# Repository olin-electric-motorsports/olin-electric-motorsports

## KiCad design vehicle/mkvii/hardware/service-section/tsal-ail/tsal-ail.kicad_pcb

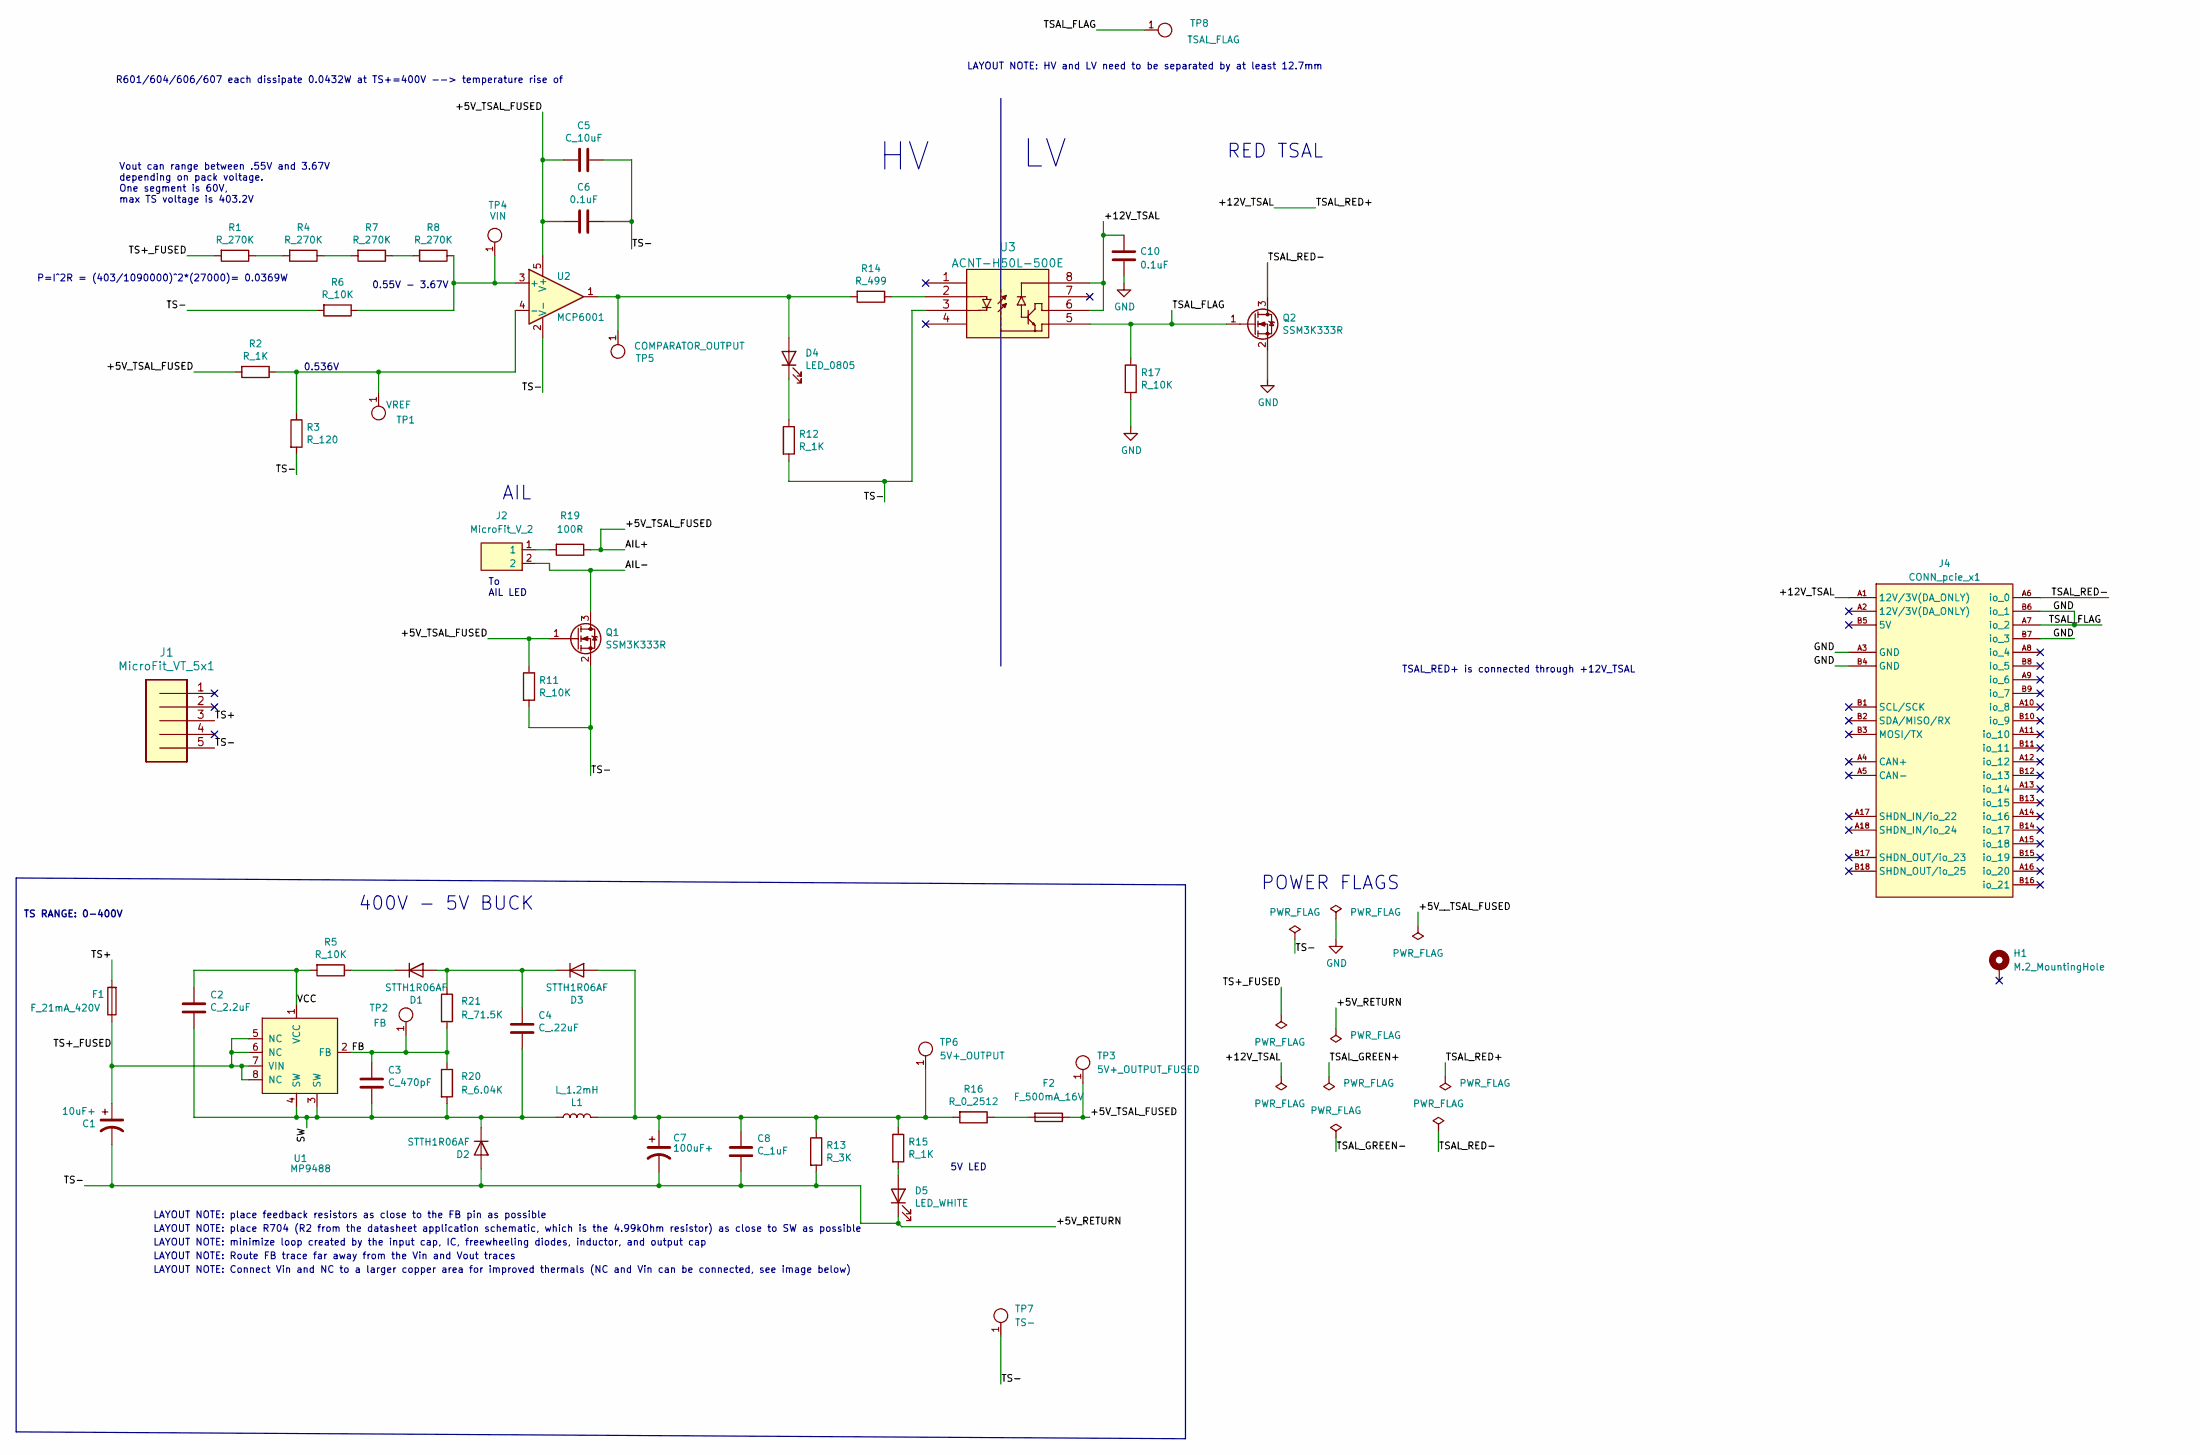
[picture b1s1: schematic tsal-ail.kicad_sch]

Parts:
C1: 10uF+; CP_Radial_D10.0mm_P5.00mm; MPN 450BXC10MEFC10X20
C2: C_2.2uF; C_0603; MPN GRM188R61E225KA12J
C3: C_470pF; C_0603; MPN 0603B471K500CT
C4: C_.22uF; C_0603; MPN CL10A224KB8NNNC
C5: C_10uF; C_0603; MPN LMK107BBJ106KALT
C6, C10: 0.1uF; C_0603; MPN CL10B104KB8NNWC
C7: 100uF+; CP_Radial_D8.0mm_P3.50mm; MPN ESK107M050AG3EA
C8: C_1uF; C_0603; MPN CL10B105KA8NNNC
D1, D2, D3: STTH1R06AF; D_SOD-128; MPN STTH1R06AF
D4: LED_0805; CHIPLED_0805; MPN LTST-C170KFKT
D5: LED_WHITE; CHIPLED_0805; MPN B1701TW--20P000314U1930
F1: F_21mA_420V; MPN B59884C0120A054
F2: F_500mA_16V; Fuse_1210; MPN 0ZCH0050FF2G
H1: M.2_MountingHole; M.2_Mount
J1: MicroFit_VT_5x1; Connector_MicroFit_VT_5x1; MPN 436500515
J2: MicroFit_V_2; MPN 0430450212
J4: CONN_pcie_x1; pcie_x1
L1: L_1.2mH; MPN RCP1317NP-122L
Q1, Q2: SSM3K333R; SOT-23F; MPN SSM3K333R,LF
R1, R4, R7, R8: R_270K; R_0603; MPN RMCF0603FT270K
R2, R12, R15: R_1K; R_0603; MPN RMCF0603FT1K00
R3: R_120; R_0603; MPN RC0603FR-13120RL
R5, R6, R11, R17: R_10K; R_0603; MPN RMCF0603FT10K0
R13: R_3K; R_0603; MPN RC0603FR-103KL
R14: R_499; R_0603; MPN RC0603FR-10499RL
R16: R_0_2512; R_2512_6332Metric; MPN CR2512-J/-000ELF
R19: 100R; R_0603; MPN RMCF0603FT100R
R20: R_6.04K; R_0603; MPN RMCF0603FT6K04
R21: R_71.5K; R_0603; MPN RMCF0603FT71K5
TP1: VREF; Test_Point_SMD; MPN 5019
TP2: FB; Test_Point_SMD; MPN 5019
TP3: 5V+_OUTPUT_FUSED; Test_Point_SMD; MPN 5019
TP4: VIN; Test_Point_SMD; MPN 5019
TP5: COMPARATOR_OUTPUT; Test_Point_SMD; MPN 5019
TP6: 5V+_OUTPUT; Test_Point_SMD; MPN 5019
TP7: TS-; Test_Point_SMD; MPN 5019
TP8: TSAL_FLAG; Test_Point_SMD; MPN 5019
U1: MP9488; Converter_DCDC_MPS_MP9488; MPN MP9488GS-Z
U2: MCP6001; SOT-353_SC-70-5; MPN MCP6001T-I/OT
U3: ACNT-H50L-500E; MPN ACNT-H50L-000E

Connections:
/+5V_RETURN: C1.2, C5.1, C6.1, C7.2, C8.2, D2.2 (A), D5.1 (K), J1.5, Q1.2 (S), R3.2, R6.2, R11.2, R12.2, R13.2, TP7.1, U2.2 (V-), U3.3
/+5V_TSAL_FUSED: C5.2, C6.2, F2.1, Q1.1 (G), R2.2, R11.1, R19.1, TP3.1, U2.5 (V+)
/+12V_TSAL: C10.1, J4.A1 (12V/3V(DA_ONLY)), U3.6, U3.8
/AIL-: J2.2, Q1.3 (D)
/FB: C3.1, R20.1, R21.2, TP2.1, U1.2 (FB)
/SW: C2.2, C3.2, C4.2, D2.1 (K), L1.1, R20.2, U1.3 (SW), U1.4 (SW)
/TS+: F1.2, J1.3
/TS+_FUSED: C1.1, F1.1, R1.2, U1.5 (NC), U1.6 (NC), U1.7 (VIN), U1.8 (NC)
/TSAL_RED-: J4.A6 (io_0), Q2.3 (D)
/VCC: C2.1, R5.2, U1.1 (VCC)
GND: C10.2, J4.A3 (GND), J4.A7 (io_2), J4.B4 (GND), J4.B6 (io_1), J4.B7 (io_3), Q2.1 (G), Q2.2 (S), R17.1, R17.2, TP8.1, U3.5
unnamed: C4.1, D1.2 (A), D3.1 (K), R21.1
unnamed: D1.1 (K), R5.1
unnamed: C7.1, C8.1, D3.2 (A), L1.2, R13.1, R15.1, R16.2, TP6.1
unnamed: D4.2 (A), R14.2, TP5.1, U2.1
unnamed: D4.1 (K), R12.1
unnamed: D5.2 (A), R15.2
unnamed: F2.2, R16.1
unnamed: J2.1, R19.2
unnamed: R1.1, R4.2
unnamed: R4.1, R7.2
unnamed: R7.1, R8.2
unnamed: R14.1, U3.2
unnamed: R6.1, R8.1, TP4.1, U2.3 (+)
unnamed: R2.1, R3.1, TP1.1, U2.4 (-)

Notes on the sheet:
TSAL_RED+ is connected through +12V_TSAL
LAYOUT NOTE: Route FB trace far away from the Vin and Vout traces
AIL
LAYOUT NOTE: minimize loop created by the input cap, IC, freewheeling diodes, inductor, and output cap
RED TSAL
LAYOUT NOTE: Connect Vin and NC to a larger copper area for improved thermals (NC and Vin can be connected, see image below)
P=I^2R = (403/1090000)^2*(27000)= 0.0369W
LAYOUT NOTE: place feedback resistors as close to the FB pin as possible
Vout can range between .55V and 3.67V depending on pack voltage. One segment is 60V, max TS voltage is 403.2V
LAYOUT NOTE: place R704 (R2 from the datasheet application schematic, which is the 4.99kOhm resistor) as close to SW as possible
LAYOUT NOTE: HV and LV need to be separated by at least 12.7mm
5V LED
POWER FLAGS
0.536V
R601/604/606/607 each dissipate 0.0432W at TS+=400V --> temperature rise of
0.55V - 3.67V
TS RANGE: 0-400V
To AIL LED
400V - 5V BUCK

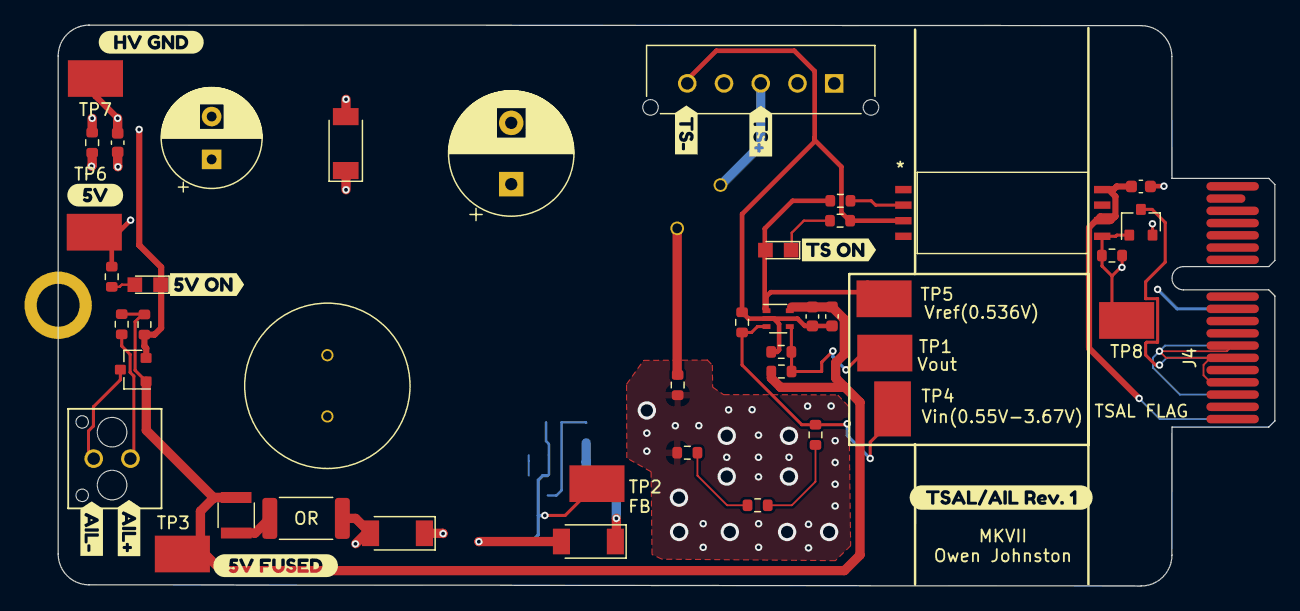
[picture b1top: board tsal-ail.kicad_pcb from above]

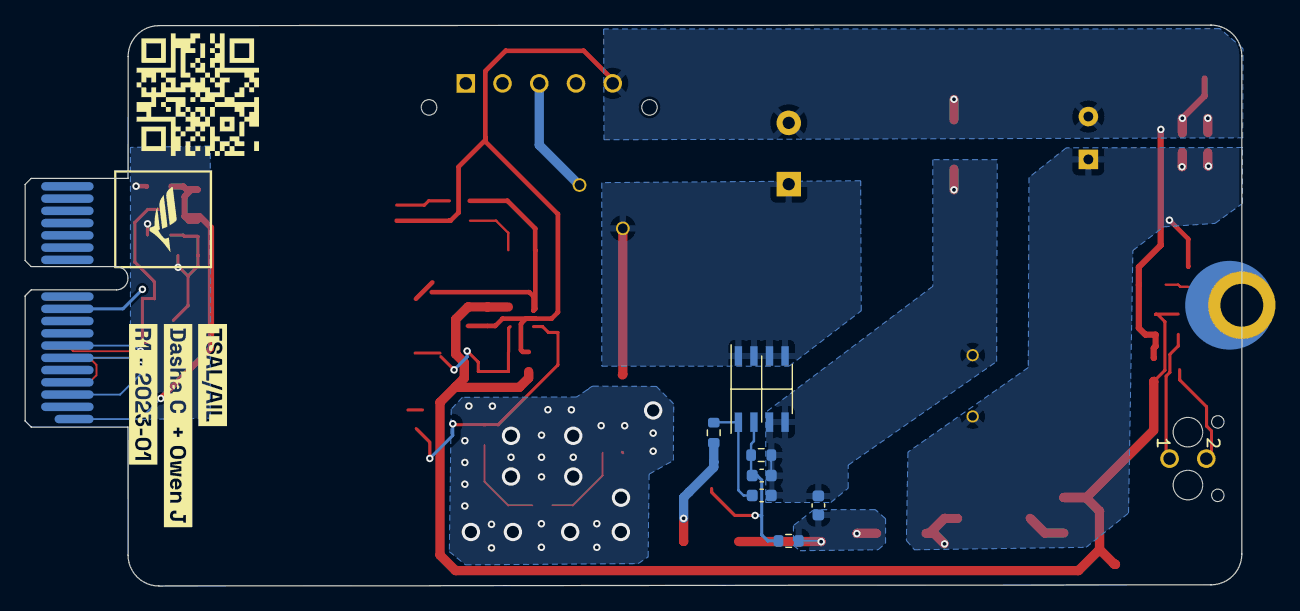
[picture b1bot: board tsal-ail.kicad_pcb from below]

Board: 2 copper layers, 99.3 x 45.8 mm, 66 parts (11 on the bottom side), 25 nets.

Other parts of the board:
QR*****: hw.oem.to/6_TSAL-AIL_1; QR_6_TSAL-AIL_1
kibuzzard-63AC91FD: G***; kibuzzard-63AC91FD
kibuzzard-63AC92E3: G***; kibuzzard-63AC92E3
kibuzzard-63AC93EB: G***; kibuzzard-63AC93EB
kibuzzard-63AC93FC: G***; kibuzzard-63AC93FC
kibuzzard-63AC9220: G***; kibuzzard-63AC9220
kibuzzard-63AC9283: G***; kibuzzard-63AC9283
kibuzzard-63AC9446: G***; kibuzzard-63AC9446
kibuzzard-63AC9456: G***; kibuzzard-63AC9456
kibuzzard-63AD023E: G***; kibuzzard-63AD023E
kibuzzard-63AD0077: G***; kibuzzard-63AD0077
kibuzzard-63BF4696: G***; kibuzzard-63BF4696
kibuzzard-63D843BA: G***; kibuzzard-63D843BA
kibuzzard-63D84460: G***; kibuzzard-63D84460

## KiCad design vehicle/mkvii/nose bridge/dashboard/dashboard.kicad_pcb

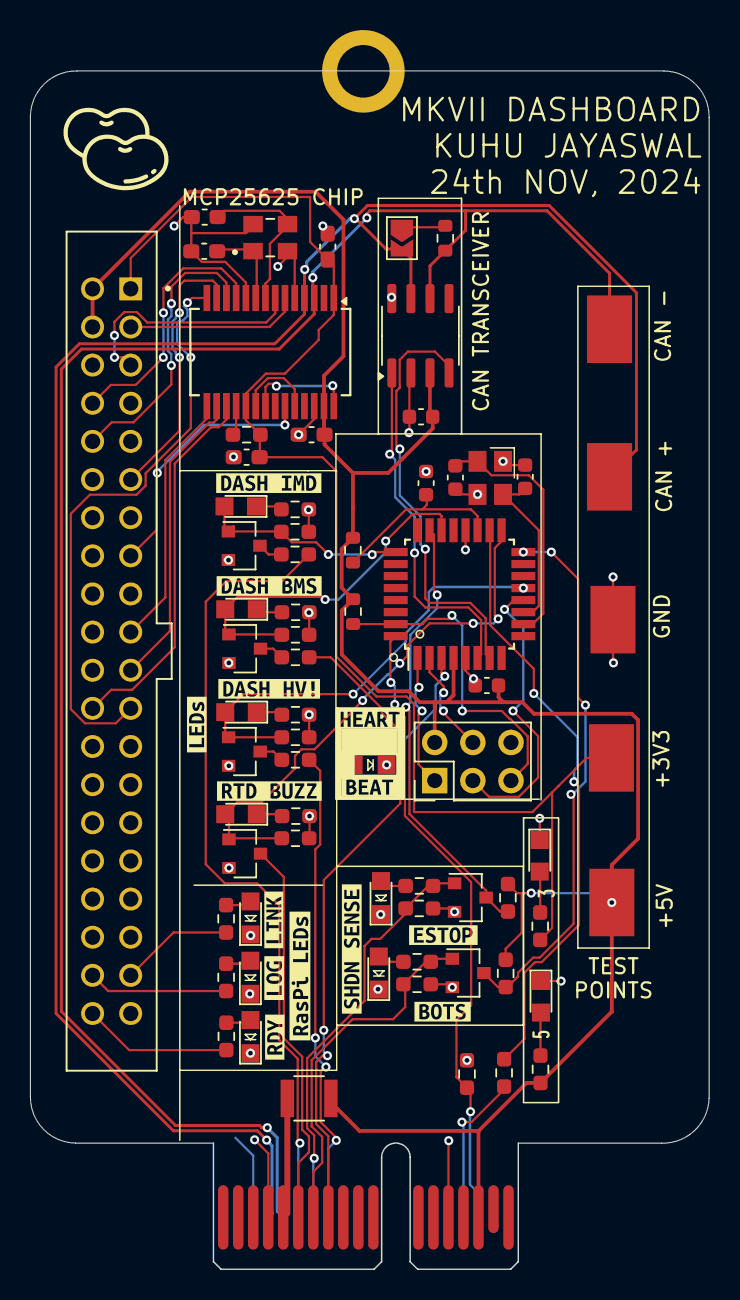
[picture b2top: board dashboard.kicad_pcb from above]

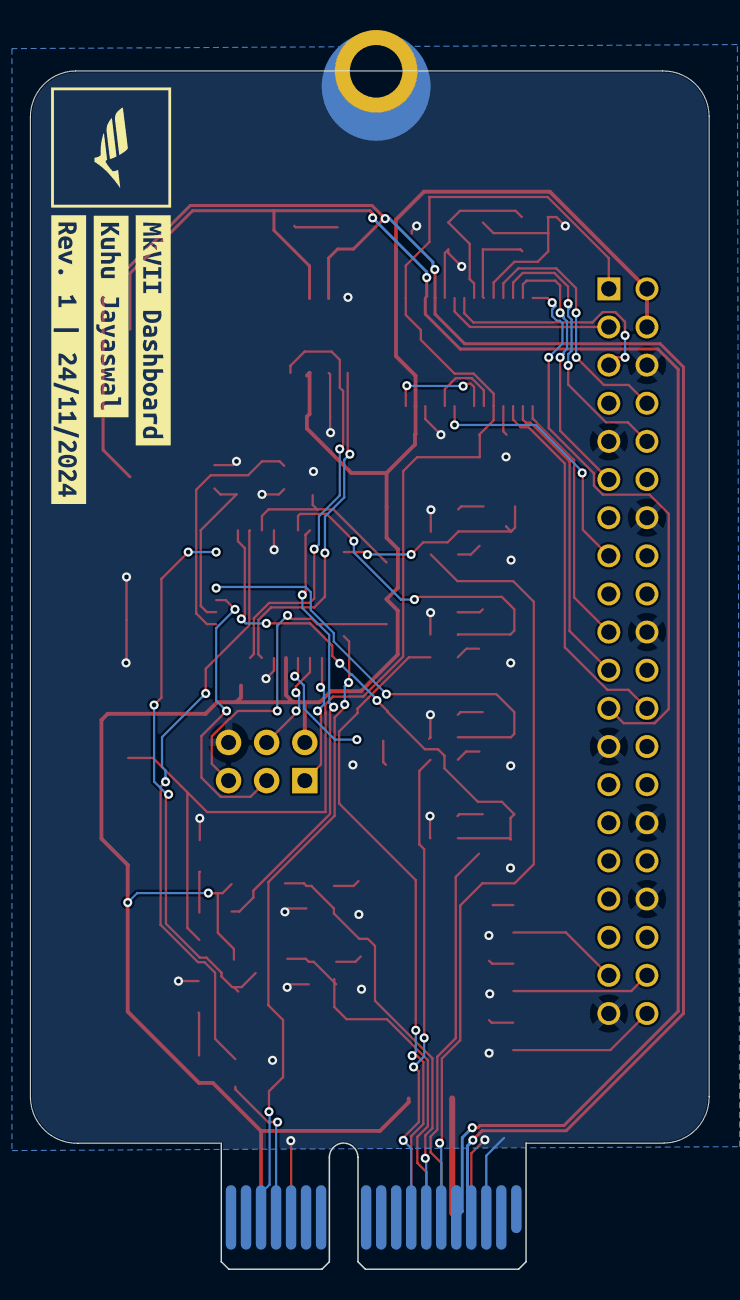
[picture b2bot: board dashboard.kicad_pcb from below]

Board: 2 copper layers, 45.2 x 79.8 mm, 90 parts (3 on the bottom side), 65 nets.

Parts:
C1, C5: 0u1F; C_0603
C2: 100pF; C_0603
C3, C4: 30pF; C_0603
C6, C7, C8: C_0.1uF; C_0603_1608Metric_Pad1.08x0.95mm_HandSolder
C9, C10: C_14pF; C_0603_1608Metric_Pad1.08x0.95mm_HandSolder
D1, D2: LED_0805; CHIPLED_0805
D3, D4, D5, D8: LED_0805; LED_0805_OEM
D6, D7: LED_BLUE; LED_0805_OEM
D9, D10, D11, D12: LED_AMBER; CHIPLED_0805
F1: F_500mA_16V; Fuse_1210
H1: CONN_MountingHole; PCIe_Mount
J1: Conn_02x20_Odd_Even; SULLINS_SFH11-PBPC-D20-ST-BK
J3: pcie_x1
J4: Conn_02x03_Odd_Even; PinHeader_2x03_P2.54mm_Vertical
JP1: SolderJumper_2_Open; SolderJumper-2_P1.3mm_Open_TrianglePad1.0x1.5mm
Q1, Q2, Q3, Q4, Q5, Q6: SSM3K333R; SOT-23F
R1, R2, R4, R5, R7, R10, R26: R_200; R_0603_1608Metric_Pad0.98x0.95mm_HandSolder
R3: 100R; R_0603
R6: R_10K; R_0603
R8: R_120_DNP; R_0603
R9, R18, R22, R25: R_10K; R_0603_1608Metric_Pad0.98x0.95mm_HandSolder
R11, R12, R13, R14, R15, R16, R17, R20, R23, R27, R28, R29, R30: R_1K; R_0603_1608Metric_Pad0.98x0.95mm_HandSolder
R21, R24: R_100K; R_0603_1608Metric_Pad0.98x0.95mm_HandSolder
TP1, TP2, TP3, TP4, TP5: Test_Point_SMD
U1: ATMEGA16M1; TQFP-32_7x7mm_Pitch0.8mm
U2: MCP2561-E-SN; SOIC-8_3.9x4.9mm_P1.27mm
U3: MCP25625-x-SS; SSOP-28_5.3x10.2mm_P0.65mm
Y1: Crystal_16MHz_18pF; Crystal_TXC7M
Y2: Crystal_8MHz_12pF; XTAL_ECS-240-8-33-AGN-TR
kibuzzard-67460C4D: G***; kibuzzard-67460C4D
kibuzzard-67461FCA: G***; kibuzzard-67461FCA
kibuzzard-67466F5D: G***; kibuzzard-67466F5D
kibuzzard-67466F8B: G***; kibuzzard-67466F8B
kibuzzard-67466FA1: G***; kibuzzard-67466FA1
kibuzzard-67468C5A: G***; kibuzzard-67468C5A
kibuzzard-674671EB: G***; kibuzzard-674671EB
kibuzzard-6746218C: G***; kibuzzard-6746218C
kibuzzard-6746500B: G***; kibuzzard-6746500B
kibuzzard-6746505F: G***; kibuzzard-6746505F
kibuzzard-6746515A: G***; kibuzzard-6746515A
kibuzzard-6746703E: G***; kibuzzard-6746703E
kibuzzard-67462150: G***; kibuzzard-67462150
kibuzzard-67462179: G***; kibuzzard-67462179
kibuzzard-67465001: G***; kibuzzard-67465001
kibuzzard-67467063: G***; kibuzzard-67467063
kibuzzard-67467243: G***; kibuzzard-67467243

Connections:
+3V3: C6.1, C7.1, J1.1, R2.1, R18.2, TP4.1, U3.1 (VIO), U3.19 (VDD)
+5V: C1.1, C5.1, C8.2, F1.1, J1.2, J1.4, J3.B16 (io_21), J4.2, R1.1, R3.1, R6.2, R22.1, R25.1, TP3.1, U1.4 (VCC), U2.3 (VDD), U3.27 (VDDA)
/AMS_LED_LOW_SIDE: J3.B8 (io_5), R14.1
/AMS_LED_LSD: D10.2 (A), Q2.1 (G), R15.1, U1.22 ((PCINT14/ADC10/ACMP1)PC6)
/BOTS_SHDN_SENSE: Q6.3 (D), R25.2, U1.16 ((PCINT2/ADC5/INT1/ACMPN0)PB2)
/CAN_+: J3.A4 (CAN+), JP1.2 (B), TP2.1, U2.7 (CANH), U3.4 (CANH)
/CAN_-: J3.A5 (CAN-), R8.2, TP5.1, U2.6 (CANL), U3.3 (CANL)
/CAN_RX: U1.7 ((PCINT11/T1/ICP1B/RXCAN)PC3), U2.4 (RXD)
/CAN_TX: U1.6 ((PCINT10/T0/TXCAN)PC2), U2.1 (TXD)
/E_STOP_SHDN_SENSE: Q5.3 (D), R22.2, U1.23 ((PCINT3/AMP0-)PB3)
/HEARTBEAT: R26.1, U1.3 ((PCINT9/PSCIN1/OC1B/~SS_A)PC1)
/HV_LED_LOW_SIDE: J3.A8 (io_4), R17.1
/HV_LED_LSD: D12.2 (A), Q4.1 (G), R30.1, U1.13 ((PCINT21/ADC2/ACMP2)PD5)
/IMD_LED_LOW_SIDE: J3.A6 (io_0), R13.1
/IMD_LED_LSD: D9.2 (A), Q1.1 (G), R11.1, U1.25 ((PCINT15/D2A/AMP2+)PC7)
/MCP25625 Chip/RX_CAN: U3.21 (RxCAN), U3.28 (RXD)
/MCP25625 Chip/TX_CAN: U3.20 (TxCAN), U3.24 (TXD)
/MCP25625 Chip/~INT: J1.11, U3.13 (~INT)
/MCP25625 Chip/~RESET: R18.1, U3.18 (~RESET)
/MCP25625 Chip/~TX1RTS: J1.3, U3.6 (~Tx1RTS)
/MCP25625 Chip/~TX2RTS: J1.5, U3.7 (~Tx2RTS)
/MISO: J1.21, U3.16 (SO)
/MOSI: J1.19, U3.15 (SI)
/PROGRAMMING_LED_1: J1.40, R4.1
/PROGRAMMING_LED_2: J1.38, R5.1
/PROGRAMMING_LED_3: J1.37, R7.1
/RESET: J4.5, R6.1, U1.31 ((PCINT24/OCD/~RESET)PE0)
/RTD_BUTTON_LED+: R10.1, U1.18 ((PCINT13/ADC9/ACMP3/AMP1+)PC5)
/RTD_BUTTON_SENSE-: J3.A16 (io_20), R9.1, U1.32 ((PCINT17/CLKO/PSCIN0)PD1)
/RTD_BUZZER_LOW_SIDE: J3.B6 (io_1), Q3.3 (D)
/RTD_BUZZER_LSD: D11.2 (A), Q3.1 (G), R28.1, U1.17 ((PCINT12/ADC8/ACMPN3/AMP1-)PC4)
/SCK: J1.23, U3.14 (SCK)
/SS_BOTS: J3.B7 (io_3), Q6.1 (G), R23.1, R24.1
/SS_ESTOP_DRIVER: J3.A7 (io_2), Q5.1 (G), R20.1, R21.1
/~CS: J1.24, U3.17 (~CS)
/~RX0BF: J1.10, U3.12 (~Rx0BF)
/~RX1BF: J1.8, U3.11 (~Rx1BF)
/~TX0RTS: J1.15, U3.23 (~Tx0RTS)
GND: C1.2, C2.2, C3.2, C4.2, C5.2, C6.2, C7.2, C8.1, C9.2, C10.2, D1.1 (K), D2.1 (K), D3.1 (K), D4.1 (K), D5.1 (K), D6.1 (K), D7.1 (K), D8.1 (K), H1.1, J1.6, J1.9, J1.14, J1.20, J1.25, J1.30, J1.34, J1.39, J3.A3 (GND), J3.B4 (GND), J3.B14 (io_17), J4.6, Q1.2 (S), Q2.2 (S), Q3.2 (S), Q4.2 (S), Q5.2 (S), Q6.2 (S), R9.2, R11.2, R12.2, R15.2, R16.2, R21.2, R24.2, R27.2, R28.2, R29.2, R30.2, TP1.1, U1.5 (GND), U1.20 (AGND), U2.2 (VSS), U2.8 (STBY), U3.5 (STBY), U3.10 (GND), U3.26 (VSS), Y1.2, Y1.4, Y2.2, Y2.4
unnamed: D1.2 (A), R1.2
unnamed: D2.2 (A), R2.2
unnamed: D3.2 (A), R4.2
unnamed: D4.2 (A), R5.2
unnamed: D5.2 (A), R7.2
unnamed: D6.2 (A), R20.2
unnamed: D7.2 (A), R23.2
unnamed: D8.2 (A), R26.2
unnamed: D9.1 (K), R27.1
unnamed: D10.1 (K), R12.1
unnamed: D11.1 (K), R16.1
unnamed: D12.1 (K), R29.1
unnamed: F1.2, J3.B5 (5V)
unnamed: J3.A15 (io_18), R10.2
unnamed: J4.1, U1.1 ((PCINT18/PSCIN2/OC1A/MISO_A)PD2)
unnamed: J4.3, U1.12 ((PCINT20/ADC1/RXD/RXLIN/ICP1A/SCK_A)PD4)
unnamed: J4.4, U1.2 ((PCINT19/TXD/TXLIN/OC0A/~SS/MOSI_A)PD3)
unnamed: JP1.1 (A), R8.1
unnamed: Q1.3 (D), R13.2
unnamed: Q2.3 (D), R14.2
unnamed: Q4.3 (D), R17.2
unnamed: C4.1, U1.10 ((PCINT25/OC0B/XTAL1)PE1), Y1.1
unnamed: C3.1, U1.11 ((PCINT26/ADC0/XTAL2)PE2), Y1.3
unnamed: C2.1, R3.2, U1.19 (AVCC)
unnamed: C9.1, U3.9 (OSC1), Y2.1
unnamed: C10.1, U3.8 (OSC2), Y2.3

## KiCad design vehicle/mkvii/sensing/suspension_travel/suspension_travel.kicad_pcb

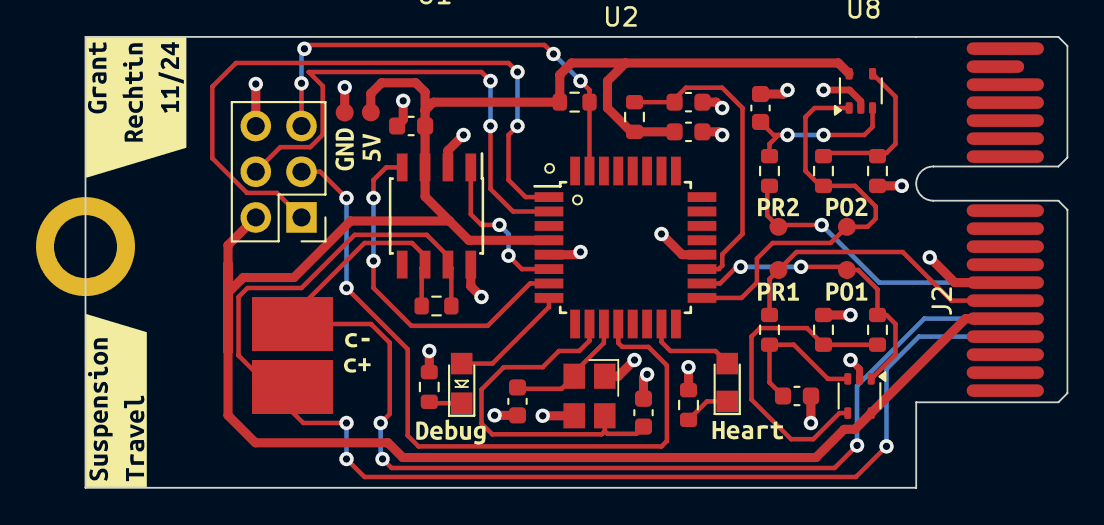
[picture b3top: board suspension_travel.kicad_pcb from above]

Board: 2 copper layers, 54.6 x 25.0 mm, 48 parts (0 on the bottom side), 25 nets.

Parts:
5VTestPoint1: TestPoint; TestPoint_Pad_D1mm
C1, C3, C6, C7: C_0.1uF; C_0603
C2: C_100pF; C_0603
C4, C5: C_30pF; C_0603
Can+Tp1: TestPoint; Test_Point_SMD
Can-TP1: TestPoint; Test_Point_SMD
D1: LED_0805; LED_0805_OEM
D2: LED_AMBER; CHIPLED_0805
GND1: TestPoint; TestPoint_Pad_D1mm
H1: CONN_MountingHole; PCIe_Mount
J1: CONN_02X03; PinHeader_2x03_P2.54mm_Vertical
J2: CONN_pcie_x1; pcie_x1
LP1_POST1, LP1_PRE1, LP2_POST1, LP2_PRE1: TestPoint; TestPoint_Pad_D1mm
R1, R4, R5, R6, R9, R10: R_100; R_0603
R2: R_120_DNP; R_0603
R3: R_10K; R_0603
R7, R8: R_200; R_0603
R11: R_1K; R_0603
U1: MCP2561-E_SN; SOIC-8_3.9x4.9mm_Pitch1.27mm_OEM
U2: ATMEGA16M1; TQFP-32_7x7mm_Pitch0.8mm
U3, U8: U_OPAMP_MCP6001; SOT-353_SC-70-5
Y1: Crystal_SMD; Crystal_TXC7M
kibuzzard-673FD6A4: G***; kibuzzard-673FD6A4
kibuzzard-673FD6B3: G***; kibuzzard-673FD6B3
kibuzzard-673FD6DC: G***; kibuzzard-673FD6DC
kibuzzard-673FD6EA: G***; kibuzzard-673FD6EA
kibuzzard-673FD6F4: G***; kibuzzard-673FD6F4
kibuzzard-673FD70C: G***; kibuzzard-673FD70C
kibuzzard-673FD675: G***; kibuzzard-673FD675
kibuzzard-673FD704: G***; kibuzzard-673FD704
kibuzzard-673FD725: G***; kibuzzard-673FD725
kibuzzard-673FD744: G***; kibuzzard-673FD744
kibuzzard-6740EEA9: G***; kibuzzard-6740EEA9
kibuzzard-6740EF04: G***; kibuzzard-6740EF04

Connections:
+5V: 5VTestPoint1.1, C1.1, C3.1, J1.2, J2.B5 (5V), R1.1, R3.1, U1.3 (VDD), U2.4 (VCC), U3.5 (V+), U8.5 (V+)
/CAN_+: Can+Tp1.1, J2.A4 (CAN+), R2.1, U1.7 (CANH)
/CAN_-: Can-TP1.1, J2.A5 (CAN-), R2.2, U1.6 (CANL)
/CAN_RX: U1.4 (RXD), U2.7 ((PCINT11/T1/ICP1B/RXCAN)PC3)
/CAN_TX: U1.1 (TXD), U2.6 ((PCINT10/T0/TXCAN)PC2)
/DEBUG_LED: D1.2 (A), U2.8 ((PCINT0/MISO/PSCOUT2A)PB0)
/Heartbeat: D2.2 (A), U2.15 ((PCINT23/ACMP0)PD7)
/MISO: J1.1, U2.1 ((PCINT18/PSCIN2/OC1A/MISO_A)PD2)
/MOSI: J1.4, U2.2 ((PCINT19/TXD/TXLIN/OC0A/~SS/MOSI_A)PD3)
/RESET: J1.5, R3.2, U2.31 ((PCINT24/OCD/~RESET)PE0)
/SCK: J1.3, U2.12 ((PCINT20/ADC1/RXD/RXLIN/ICP1A/SCK_A)PD4)
/lp1_Vout: J2.B6 (io_1), LP1_PRE1.1, R5.1
/lp1_fVout: LP1_POST1.1, R9.1, U2.18 ((PCINT13/ADC9/ACMP3/AMP1+)PC5), U3.1
/lp2_Vout: J2.A7 (io_2), LP2_PRE1.1, R6.1
/lp2_fVout: LP2_POST1.1, R10.1, U2.17 ((PCINT12/ADC8/ACMPN3/AMP1-)PC4), U8.1
GND: C1.2, C2.2, C3.2, C4.2, C5.2, C6.2, C7.2, GND1.1, H1.1, J1.6, J2.A3 (GND), J2.A6 (io_0), J2.B4 (GND), J2.B7 (io_3), R4.2, R7.1, R8.1, R11.2, U1.2 (VSS), U1.8 (STBY), U2.5 (GND), U2.20 (AGND), U3.2 (V-), U8.2 (V-), Y1.2, Y1.4
unnamed: D1.1 (K), R4.1
unnamed: D2.1 (K), R11.1
unnamed: C5.1, U2.10 ((PCINT25/OC0B/XTAL1)PE1), Y1.3
unnamed: C4.1, U2.11 ((PCINT26/ADC0/XTAL2)PE2), Y1.1
unnamed: C2.1, R1.2, U2.19 (AVCC)
unnamed: C6.1, R5.2, U3.3 (+)
unnamed: R7.2, R9.2, U3.4 (-)
unnamed: C7.1, R6.2, U8.3 (+)
unnamed: R8.2, R10.2, U8.4 (-)

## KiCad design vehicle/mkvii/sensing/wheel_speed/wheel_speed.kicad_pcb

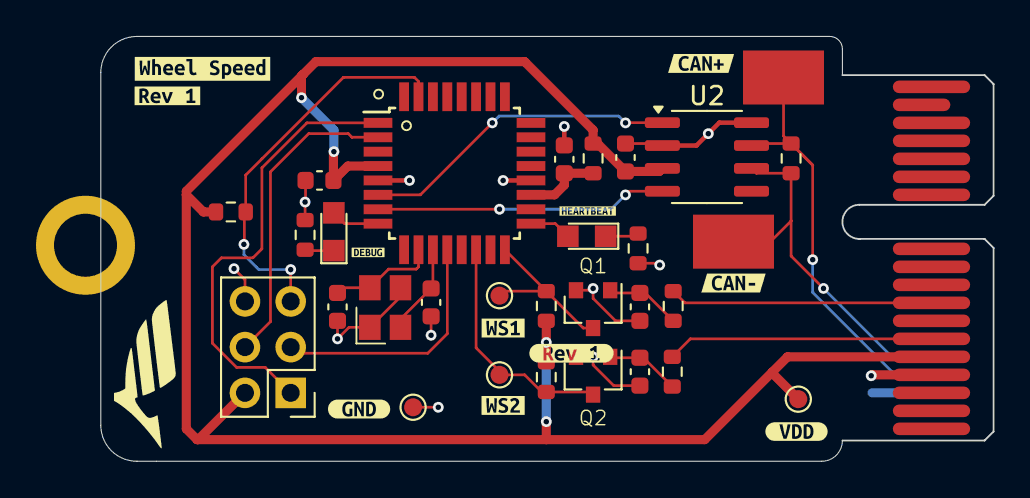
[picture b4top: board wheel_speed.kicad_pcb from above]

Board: 2 copper layers, 49.6 x 23.6 mm, 43 parts (1 on the bottom side), 23 nets.

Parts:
C1: C_0.1uF; C_0603
C2: C_100pF; C_0603
C3: 0u1F; C_0603
C4, C5: C_30pF; C_0603
C6, C7: 10nF; C_0603
D1, D2: LED_BLUE; CHIPLED_0805
GND1: TestPoint; TestPoint_Pad_D1.0mm
J1: CONN_02x03; PinHeader_2x03_P2.54mm_Vertical
J2: pcie_x1
Q1, Q2: SSM3K333R; SOT-23F
R1, R4, R9: R_100; R_0603
R2: R_120_DNP; R_0603
R3: R_10K; R_0603
R5, R7: 1K; R_0603
R6, R8: R_1K_DNP; R_0603
TP1, TP2: TP_SMD; Test_Point_SMD
U1: ATMEGA16M1; TQFP-32_7x7mm_Pitch0.8mm
U2: MCP2561-E-SN; SOIC-8_3.9x4.9mm_P1.27mm
VDD1: TestPoint; TestPoint_Pad_D1.0mm
WS1, WS2: TestPoint; TestPoint_Pad_D1.0mm
Y1: Crystal_16MHz_18pF; Crystal_TXC7M
kibuzzard-673FD414: G***; kibuzzard-673FD414
kibuzzard-6733FF5C: G***; kibuzzard-6733FF5C
kibuzzard-6733FF7D: G***; kibuzzard-6733FF7D
kibuzzard-6733FF15: G***; kibuzzard-6733FF15
kibuzzard-6733FF25: G***; kibuzzard-6733FF25
kibuzzard-6733FF69: G***; kibuzzard-6733FF69
kibuzzard-67434F9F: G***; kibuzzard-67434F9F
kibuzzard-674351E2: G***; kibuzzard-674351E2
kibuzzard-674352C6: G***; kibuzzard-674352C6
kibuzzard-67435037: G***; kibuzzard-67435037
kibuzzard-67435047: G***; kibuzzard-67435047
kibuzzard-67435202: G***; kibuzzard-67435202

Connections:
+5V: C1.1, C3.2, J1.2, J2.B5 (5V), R1.1, R3.2, R6.1, R8.1, U1.4 (VCC), U2.3 (VDD), VDD1.1
/CAN_+: J2.A4 (CAN+), R2.1, TP2.1, U2.7 (CANH)
/CAN_-: J2.A5 (CAN-), R2.2, TP1.1, U2.6 (CANL)
/CAN_RX: U1.7 ((PCINT11/T1/ICP1B/RXCAN)PC3), U2.4 (RXD)
/CAN_TX: U1.6 ((PCINT10/T0/TXCAN)PC2), U2.1 (TXD)
/DEBUG_LED: D1.2 (A), U1.8 ((PCINT0/MISO/PSCOUT2A)PB0)
/HEARTBEAT_LED: D2.2 (A), U1.17 ((PCINT12/ADC8/ACMPN3/AMP1-)PC4)
/MISO: J1.1, U1.1 ((PCINT18/PSCIN2/OC1A/MISO_A)PD2)
/MOSI: J1.4, U1.2 ((PCINT19/TXD/TXLIN/OC0A/~SS/MOSI_A)PD3)
/RESET: J1.5, R3.1, U1.31 ((PCINT24/OCD/~RESET)PE0)
/SCK: J1.3, U1.12 ((PCINT20/ADC1/RXD/RXLIN/ICP1A/SCK_A)PD4)
/ws1_Vout: J2.B8 (io_5), R7.1
/ws1_fVout: Q1.3 (D), R8.2, U1.16 ((PCINT2/ADC5/INT1/ACMPN0)PB2), WS1.1
/ws2_Vout: J2.B6 (io_1), R5.1
/ws2_fVout: Q2.3 (D), R6.2, U1.14 ((PCINT22/ADC3/INT0/ACMPN2)PD6), WS2.1
GND: C1.2, C2.2, C3.1, C4.2, C5.2, C6.2, C7.2, GND1.1, J1.6, J2.A3 (GND), J2.B4 (GND), Q1.2 (S), Q2.2 (S), R4.2, R9.2, U1.5 (GND), U1.20 (AGND), U2.2 (VSS), U2.8 (STBY), Y1.2, Y1.4
unnamed: D1.1 (K), R4.1
unnamed: D2.1 (K), R9.1
unnamed: C6.1, Q1.1 (G), R7.2
unnamed: C7.1, Q2.1 (G), R5.2
unnamed: C5.1, U1.10 ((PCINT25/OC0B/XTAL1)PE1), Y1.3
unnamed: C4.1, U1.11 ((PCINT26/ADC0/XTAL2)PE2), Y1.1
unnamed: C2.1, R1.2, U1.19 (AVCC)

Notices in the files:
parts and their libraries:
Copyright 2021 Accelerated Designs. All rights reserved.
